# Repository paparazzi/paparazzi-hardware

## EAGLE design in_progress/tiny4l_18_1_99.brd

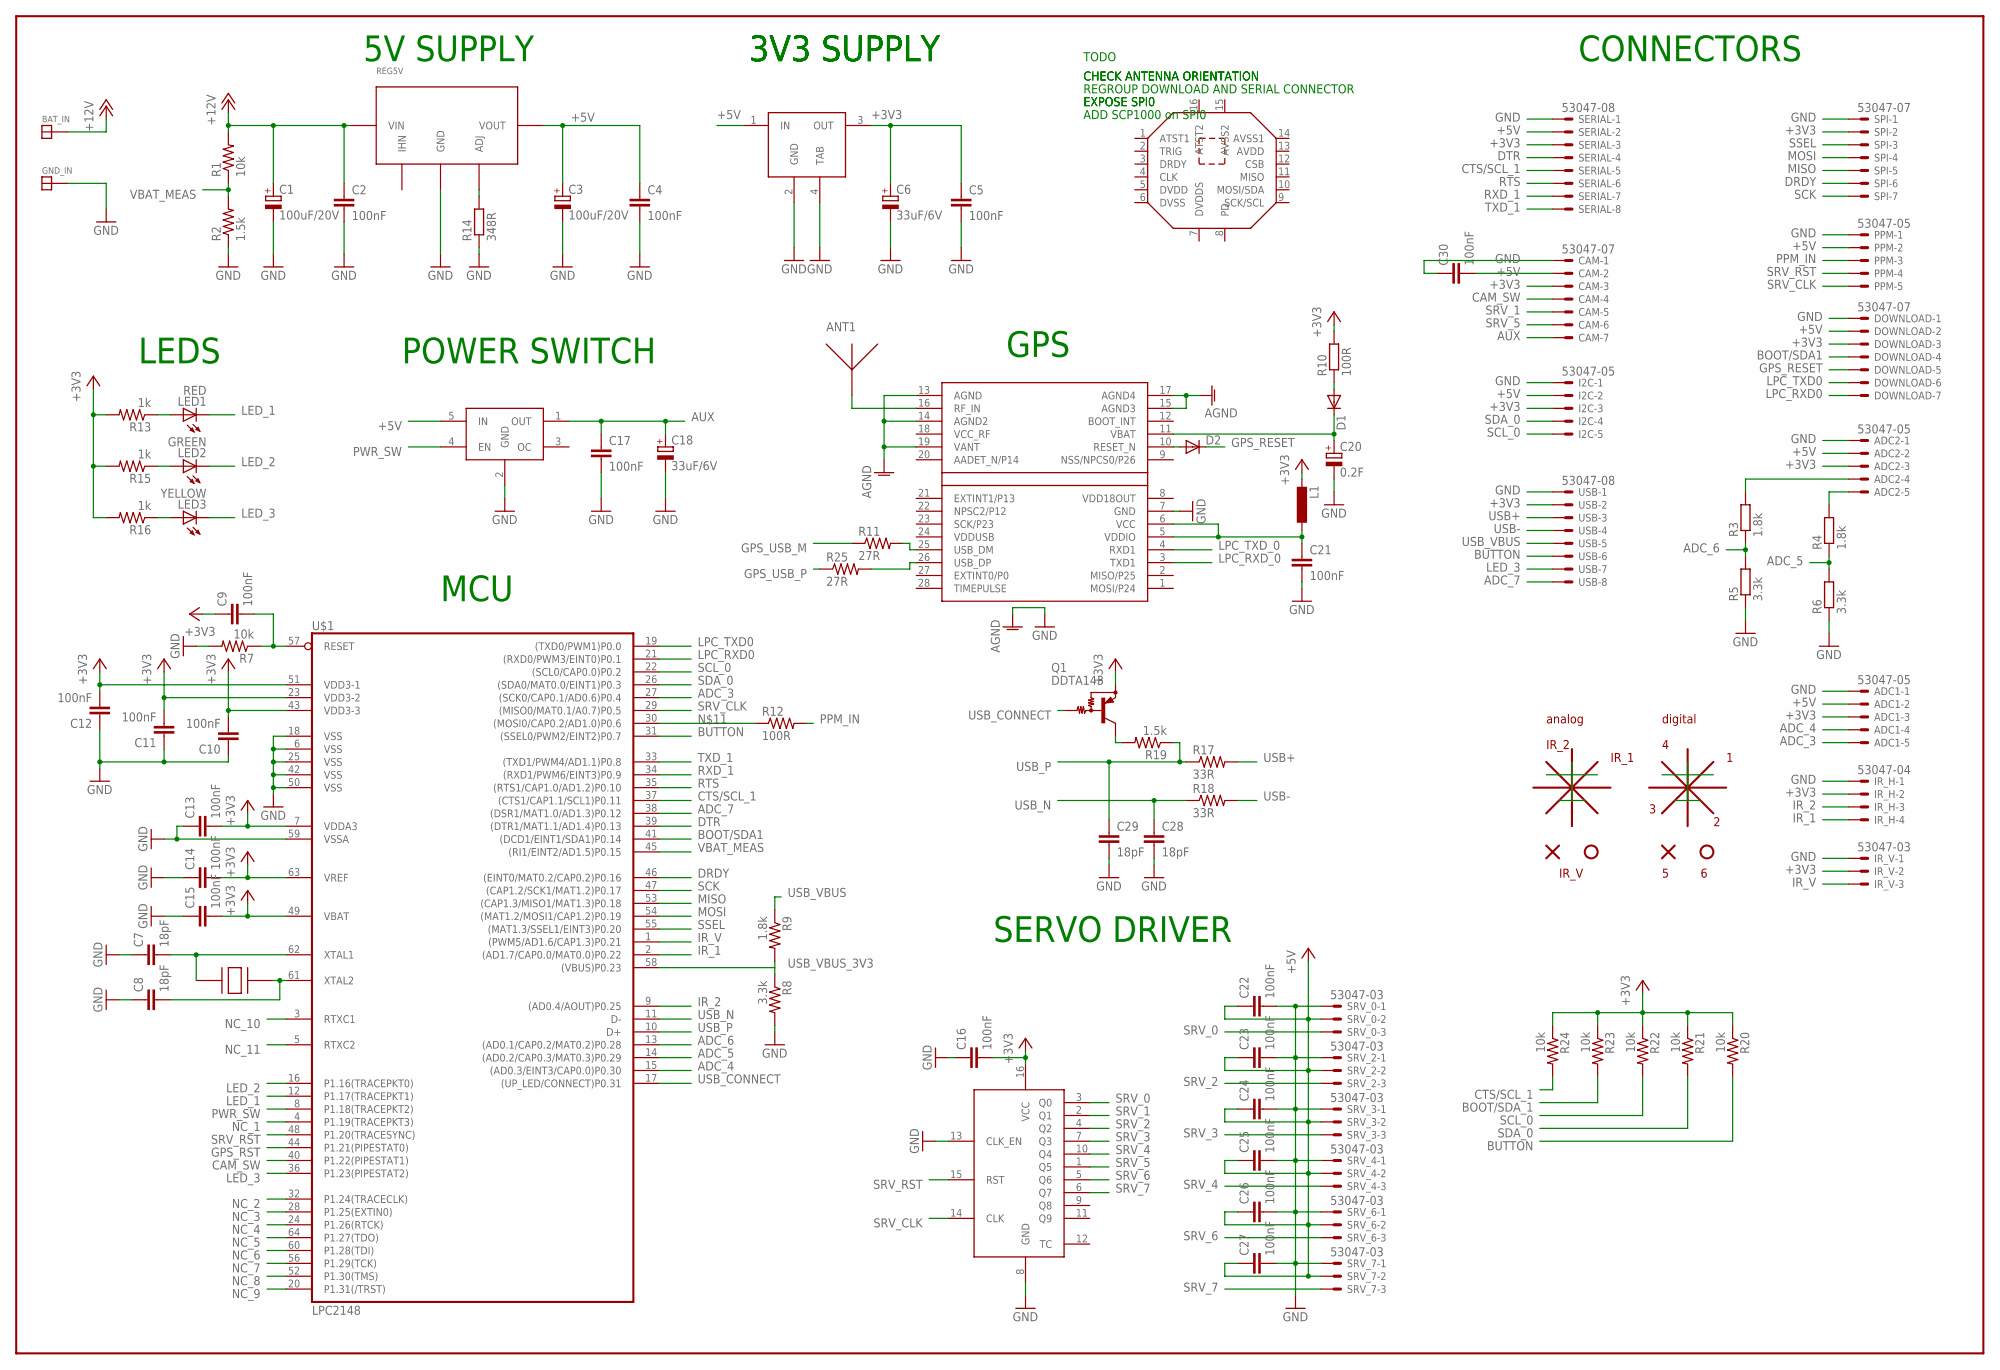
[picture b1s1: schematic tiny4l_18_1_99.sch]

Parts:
ADC1, ADC2: 53047-05
ANT1: GPS_ANT_1318; ANT_18
BAT_IN: SOLDER_PAD150_75; SOLD_PAD_150_75
C1, C3: 100uF/20V; SMC_D
C2, C4, C5, C9, C10, C11, C12, C13, C14, C15, C16, C17, C21, C22, C23, C24, C25, C26, C27, C30: 100nF; C0603
C6, C18: 33uF/6V; CT3216
C7, C8, C28, C29: 18pF; C0603
C20: 0.2F; PANA_J1_BIS
CAM: 53047-07
D1, D2: DIODE-SOD523; SOD523
DOWNLOAD: 53047-07
GND_IN: SOLDER_PAD150_75; SOLD_PAD_150_75
I2C: 53047-05
IR_H: 53047-04
IR_V: 53047-03
L1: L-EUL2012C; L2012C
LED1: RED; CHIP-LED0805
LED2: GREEN; CHIP-LED0805
LED3: YELLOW; CHIP-LED0805
PPM: 53047-05
Q1: DDTA143; SC59-BEC
R1, R7, R20, R21, R22, R23, R24: 10k; R0603
R2, R19: 1.5k; R0603
R3, R4, R9: 1.8k; R0603
R5, R6, R8: 3.3k; R0603
R10, R12: 100R; R0603
R11, R25: 27R; R0603
R13, R15, R16: 1k; R0603
R14: 348R; R0603
R17, R18: 33R; R0603
REG5V: PTH
SERIAL: 53047-08
SPI: 53047-07
SRV_0, SRV_2, SRV_3, SRV_4, SRV_6, SRV_7: 53047-03
U$1: LPC2148; SQFP-S-10X10-64
U$2: LEA-4P; LEA-LA
U$3: LM3940IMP-3.3; SOT223-R
U$4: CRYSTAL_CTS; CTS_CRYSTAL
U$5: CD4017B; TSSOP16
U$6: TPS2051B; SOT23-5L
U$7: SCP1000
USB: 53047-08

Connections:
+3V3: ADC1.3, ADC2.3, C5.1, C6.+, C9.1, C10.2, C11.2, C12.2, C13.2, C14.2, C15.2, C16.2, CAM.3, DOWNLOAD.3, I2C.3, IR_H.2, IR_V.2, L1.2, Q1.E, R10.2, R13.2, R15.2, R16.2, R20.1, R21.1, R22.1, R23.1, R24.1, SERIAL.3, SPI.2, U$1.7 (VDDA3), U$1.23 (VDD3-2), U$1.43 (VDD3-3), U$1.49 (VBAT), U$1.51 (VDD3-1), U$1.63 (VREF), U$3.3 (OUT), U$5.16 (VCC), USB.2
+5V: ADC1.2, ADC2.2, C3.+, C4.1, C22.1, C23.1, C24.1, C25.1, C26.1, C27.1, C30.2, CAM.2, DOWNLOAD.2, I2C.2, PPM.2, REG5V.P$3 (VOUT), SERIAL.2, SRV_0.2, SRV_2.2, SRV_3.2, SRV_4.2, SRV_6.2, SRV_7.2, U$3.1 (IN), U$6.5 (IN)
+12V: BAT_IN.P$1, C1.+, C2.1, R1.2, REG5V.P$1 (VIN)
ADC_3: ADC1.5, U$1.27 ((SCK0/CAP0.1/AD0.6)P0.4)
ADC_4: ADC1.4, U$1.15 ((AD0.3/EINT3/CAP0.0)P0.30)
ADC_5: R4.1, R6.2, U$1.14 ((AD0.2/CAP0.3/MAT0.3)P0.29)
ADC_6: R3.1, R5.2, U$1.13 ((AD0.1/CAP0.2/MAT0.2)P0.28)
ADC_7: U$1.38 ((DSR1/MAT1.0/AD1.3)P0.12), USB.8
AGND: U$2.13 (AGND), U$2.14 (AGND2), U$2.15 (AGND3), U$2.17 (AGND4), U$2.19 (VANT)
AUX: C17.1, C18.+, CAM.7, U$6.1 (OUT)
BOOT/SDA1: DOWNLOAD.4, U$1.41 ((DCD1/EINT1/SDA1)P0.14)
BOOT/SDA_1: R23.2
BUTTON: R20.2, U$1.31 ((SSEL0/PWM2/EINT2)P0.7), USB.6
CAM_SW: CAM.4, U$1.40 (P1.22(PIPESTAT1))
CTS/SCL_1: R24.2, SERIAL.5, U$1.37 ((CTS1/CAP1.1/SCL1)P0.11)
DRDY: SPI.6, U$1.46 ((EINT0/MAT0.2/CAP0.2)P0.16)
DTR: SERIAL.4, U$1.39 ((DTR1/MAT1.1/AD1.4)P0.13)
GND: ADC1.1, ADC2.1, C1.-, C2.2, C3.-, C4.2, C5.2, C6.-, C7.1, C8.1, C10.1, C11.1, C12.1, C13.1, C14.1, C15.1, C16.1, C17.2, C18.-, C20.MINUS (-), C21.2, C22.2, C23.2, C24.2, C25.2, C26.2, C27.2, C28.2, C29.2, C30.1, CAM.1, DOWNLOAD.1, GND_IN.P$1, I2C.1, IR_H.1, IR_V.1, PPM.1, R2.1, R5.1, R6.1, R7.2, R8.2, R14.1, REG5V.P$2 (GND), SERIAL.1, SPI.1, SRV_0.1, SRV_2.1, SRV_3.1, SRV_4.1, SRV_6.1, SRV_7.1, U$1.6 (VSS), U$1.18 (VSS), U$1.25 (VSS), U$1.42 (VSS), U$1.50 (VSS), U$1.59 (VSSA), U$2.7 (GND), U$3.2 (GND), U$3.4 (TAB), U$5.8 (GND), U$5.13 (CLK_EN), U$6.2 (GND), USB.1
GPS_RESET: D2.C, DOWNLOAD.5
GPS_RST: U$1.44 (P1.21(PIPESTAT0))
GPS_USB_M: R11.1
GPS_USB_P: R25.1
IR_1: IR_H.4, U$1.2 ((AD1.7/CAP0.0/MAT0.0)P0.22)
IR_2: IR_H.3, U$1.9 ((AD0.4/AOUT)P0.25)
IR_V: IR_V.3, U$1.1 ((PWM5/AD1.6/CAP1.3)P0.21)
LED_1: LED1.C, U$1.12 (P1.17(TRACEPKT1))
LED_2: LED2.C, U$1.16 (P1.16(TRACEPKT0))
LED_3: LED3.C, U$1.36 (P1.23(PIPESTAT2)), USB.7
LPC_RESET: C9.2, R7.1, U$1.57 (RESET)
LPC_RXD0: DOWNLOAD.7, U$1.21 ((RXD0/PWM3/EINT0)P0.1)
LPC_RXD_0: U$2.3 (TXD1)
LPC_TXD0: DOWNLOAD.6, U$1.19 ((TXD0/PWM1)P0.0)
LPC_TXD_0: U$2.4 (RXD1)
MISO: SPI.5, U$1.53 ((CAP1.3/MISO1/MAT1.3)P0.18)
MOSI: SPI.4, U$1.54 ((MAT1.2/MOSI1/CAP1.2)P0.19)
unnamed: LED1.A, R13.1
unnamed: C7.2, U$1.62 (XTAL1), U$4.P$1
unnamed: D1.A, R10.1
unnamed: C8.2, U$1.61 (XTAL2), U$4.P$3
unnamed: R14.2, REG5V.P$4 (ADJ)
unnamed: LED2.A, R15.1
unnamed: LED3.A, R16.1
unnamed: ANT1.P$1, U$2.16 (RF_IN)
unnamed: D2.A, U$2.10 (RESET_N)
unnamed: C20.PLUS (+), D1.C, U$2.11 (VBAT)
unnamed: R12.1, U$1.30 ((MOSI0/CAP0.2/AD1.0)P0.6)
unnamed: R8.1, R9.2
unnamed: C21.1, L1.1, U$2.5 (VDDIO), U$2.6 (VCC)
unnamed: Q1.C, R19.2
unnamed: R11.2, U$2.25 (USB_DM)
unnamed: R25.2, U$2.26 (USB_DP)
unnamed: ADC2.4, R3.2
unnamed: ADC2.5, R4.2
NC_1: U$1.4 (P1.19(TRACEPKT3))
NC_2: U$1.32 (P1.24(TRACECLK))
NC_3: U$1.28 (P1.25(EXTIN0))
NC_4: U$1.24 (P1.26(RTCK))
NC_5: U$1.64 (P1.27(TDO))
NC_6: U$1.60 (P1.28(TDI))
NC_7: U$1.56 (P1.29(TCK))
NC_8: U$1.52 (P1.30(TMS))
NC_9: U$1.20 (P1.31(/TRST))
NC_10: U$1.3 (RTXC1)
NC_11: U$1.5 (RTXC2)
PPM_IN: PPM.3, R12.2
PWR_SW: U$1.8 (P1.18(TRACEPKT2)), U$6.4 (EN)
RTS: SERIAL.6, U$1.35 ((RTS1/CAP1.0/AD1.2)P0.10)
RXD_1: SERIAL.7, U$1.34 ((RXD1/PWM6/EINT3)P0.9)
SCK: SPI.7, U$1.47 ((CAP1.2/SCK1/MAT1.2)P0.17)
SCL_0: I2C.5, R22.2, U$1.22 ((SCL0/CAP0.0)P0.2)
SDA_0: I2C.4, R21.2, U$1.26 ((SDA0/MAT0.0/EINT1)P0.3)
SRV_0: SRV_0.3, U$5.3 (Q0)
SRV_1: CAM.5, U$5.2 (Q1)
SRV_2: SRV_2.3, U$5.4 (Q2)
SRV_3: SRV_3.3, U$5.7 (Q3)
SRV_4: SRV_4.3, U$5.10 (Q4)
SRV_5: CAM.6, U$5.1 (Q5)
SRV_6: SRV_6.3, U$5.5 (Q6)
SRV_7: SRV_7.3, U$5.6 (Q7)
SRV_CLK: PPM.5, U$1.29 ((MISO0/MAT0.1/A0.7)P0.5), U$5.14 (CLK)
SRV_RST: PPM.4, U$1.48 (P1.20(TRACESYNC)), U$5.15 (RST)
SSEL: SPI.3, U$1.55 ((MAT1.3/SSEL1/EINT3)P0.20)
TXD_1: SERIAL.8, U$1.33 ((TXD1/PWM4/AD1.1)P0.8)
USB+: R17.2, USB.3
USB-: R18.2, USB.4
USB_CONNECT: Q1.B, U$1.17 ((UP_LED/CONNECT)P0.31)
USB_N: C28.1, R18.1, U$1.11 (D-)
USB_P: C29.1, R17.1, R19.1, U$1.10 (D+)
USB_VBUS: R9.1, USB.5
USB_VBUS_3V3: U$1.58 ((VBUS)P0.23)
VBAT_MEAS: R1.1, R2.2, U$1.45 ((RI1/EINT2/AD1.5)P0.15)
VCC_RF: U$2.18 (VCC_RF)
VDD18OUT: U$2.8 (VDD18OUT)

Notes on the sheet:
5V SUPPLY
3V3 SUPPLY
MCU
GPS
LEDS
POWER SWITCH
SERVO DRIVER
CONNECTORS
CHECK ANTENNA ORIENTATION
TODO
REGROUP DOWNLOAD AND SERIAL CONNECTOR
EXPOSE SPI0
ADD SCP1000 on SPI0
IR_V
IR_2
IR_1
analog
digital

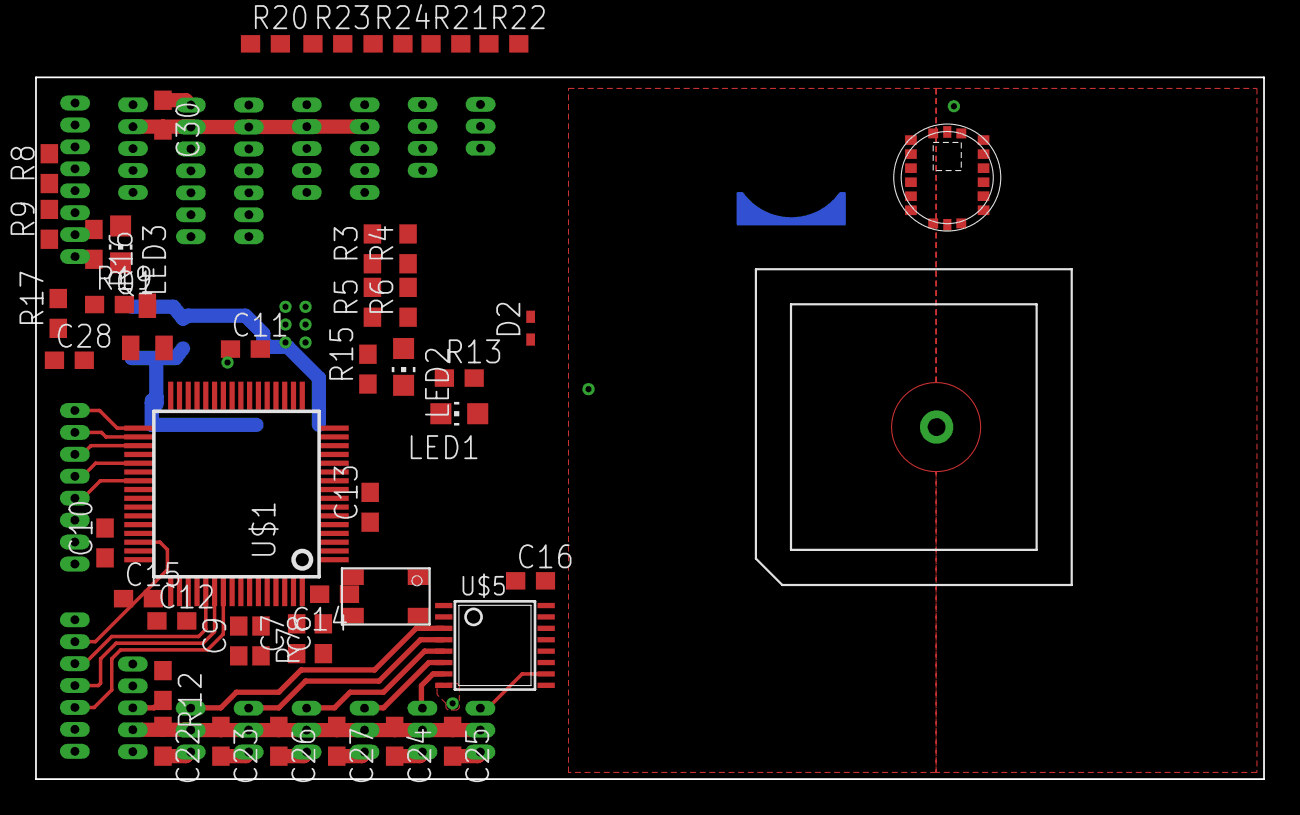
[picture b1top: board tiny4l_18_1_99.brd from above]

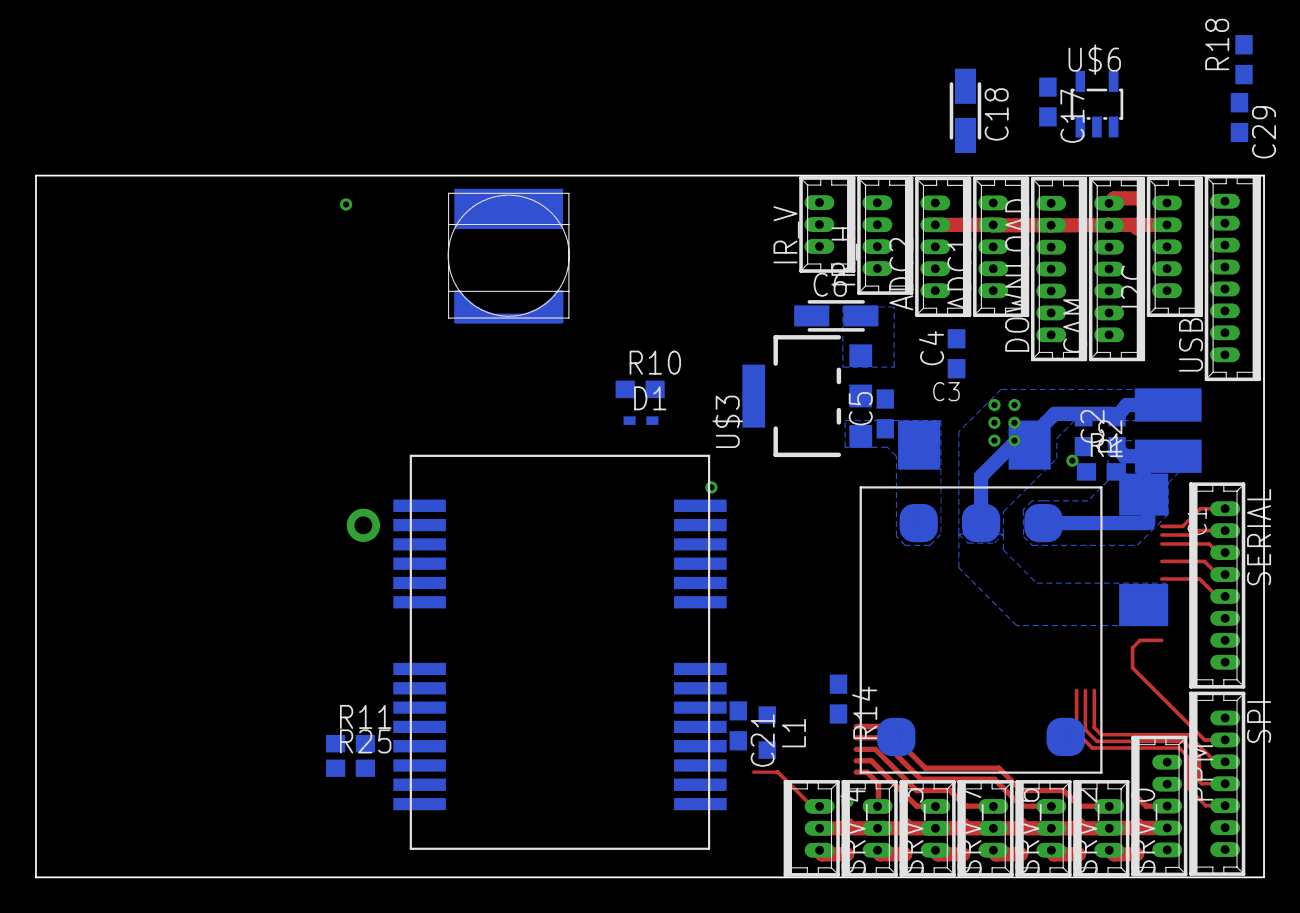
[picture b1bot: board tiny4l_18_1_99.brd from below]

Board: 4 copper layers, 70.0 x 40.0 mm, 89 parts (43 on the bottom side), 73 nets.

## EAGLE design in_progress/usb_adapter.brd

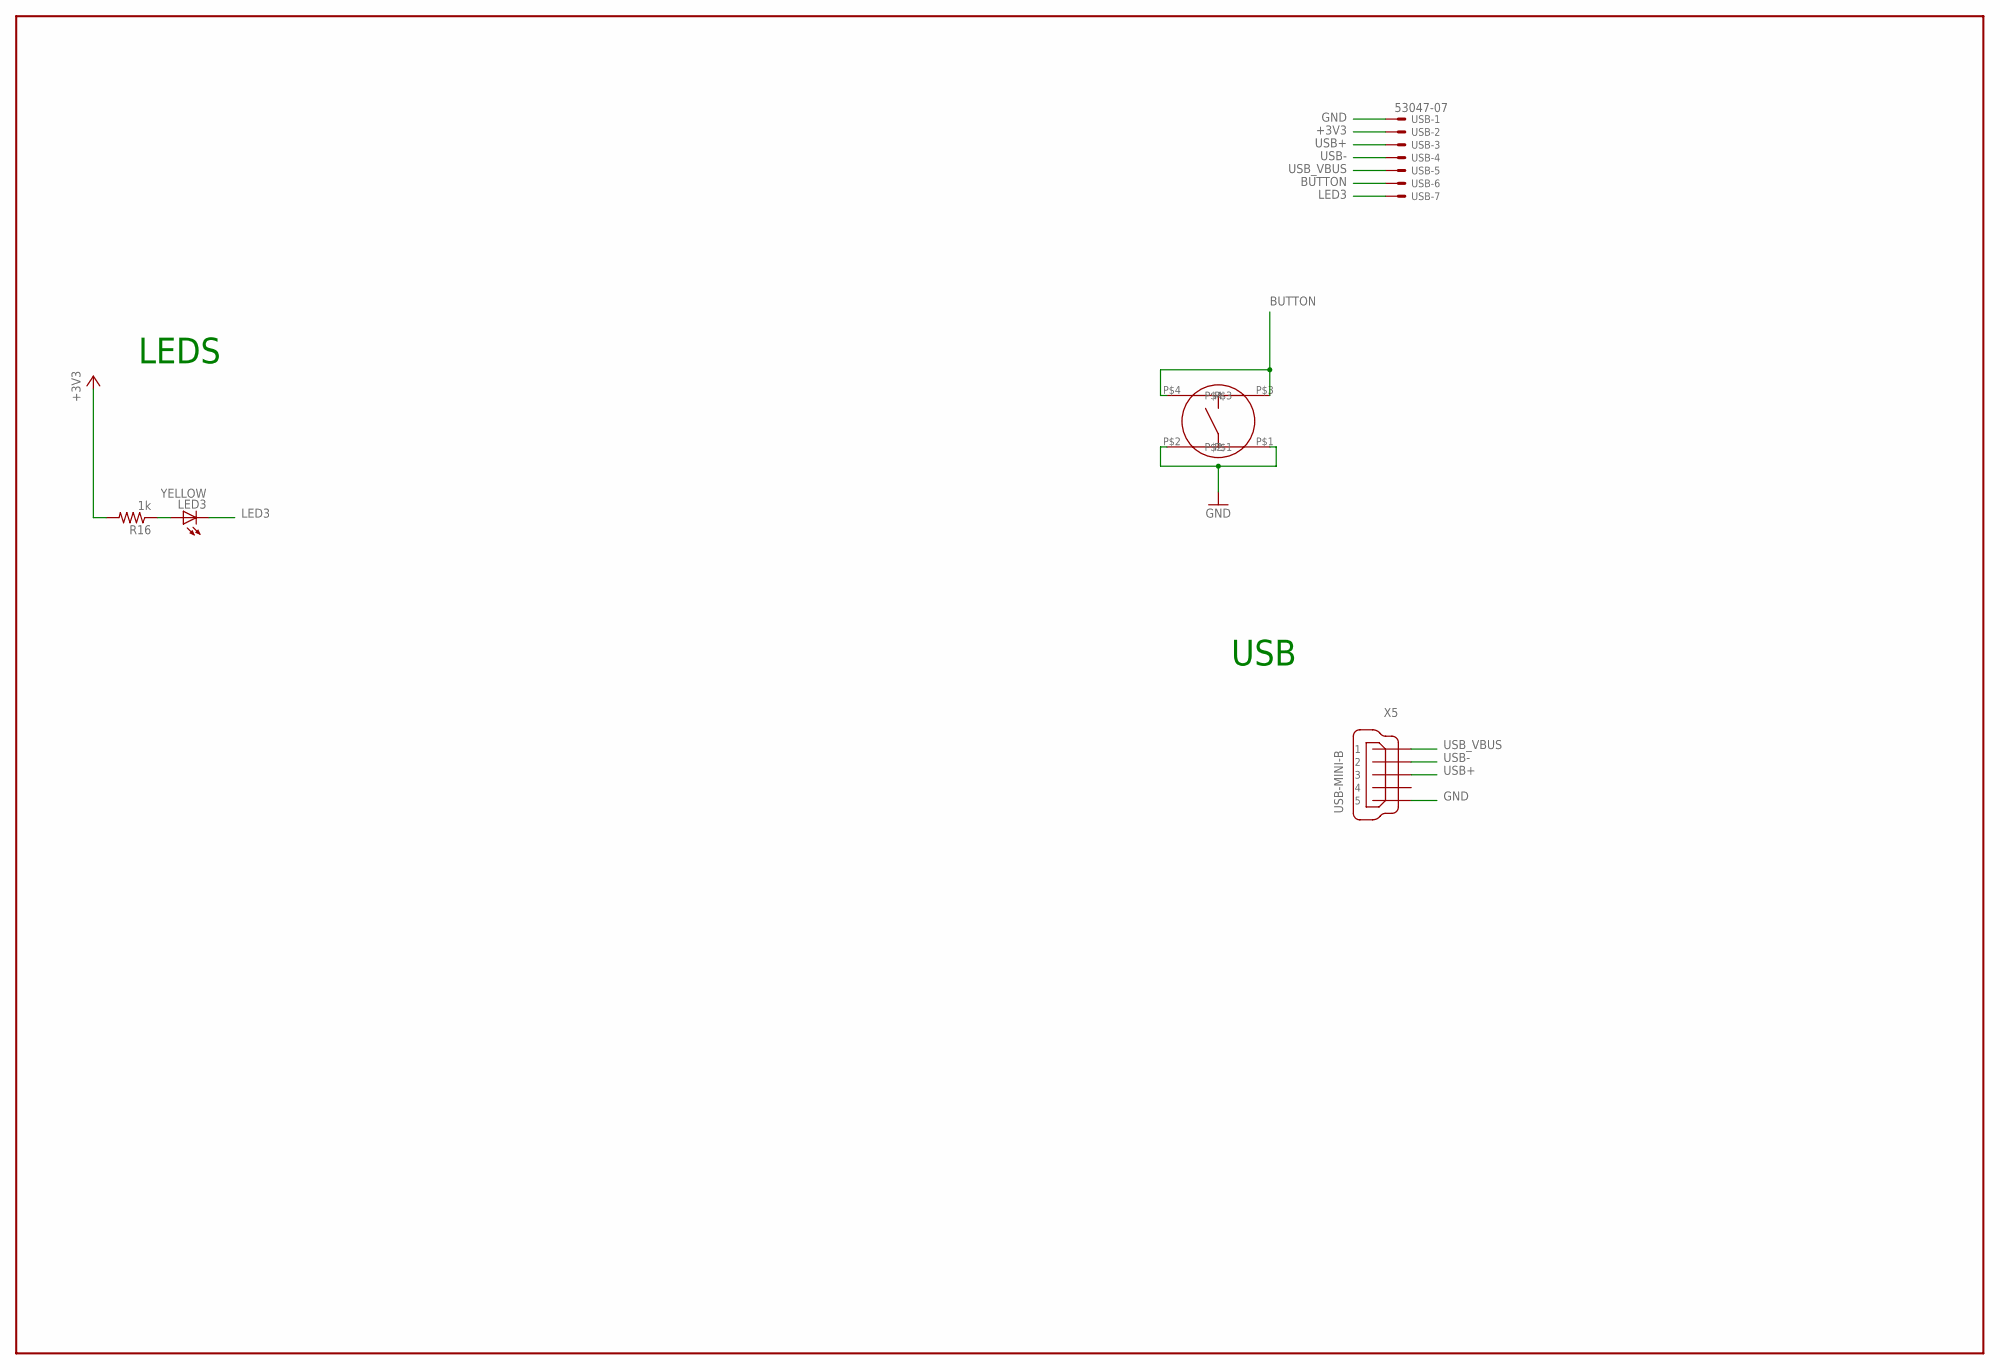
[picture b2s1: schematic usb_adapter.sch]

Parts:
LED3: YELLOW; CHIP-LED0805
R16: 1k; R0603@1
SW1: B3S
USB: 53047-07
X5: USB-MINI-B; UX60-MB-5ST

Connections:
+3V3: R16.2, USB.2
BUTTON: SW1.P$3, SW1.P$4, USB.6
GND: SW1.P$1, SW1.P$2, USB.1, X5.5
LED3: LED3.C, USB.7
unnamed: LED3.A, R16.1
USB+: USB.3, X5.3
USB-: USB.4, X5.2
USB_VBUS: USB.5, X5.1

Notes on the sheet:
LEDS
USB

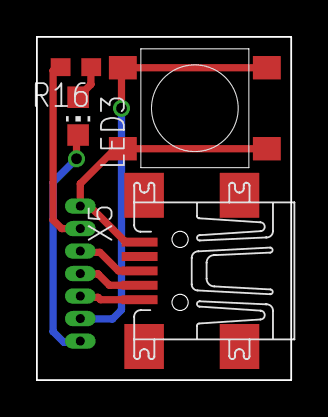
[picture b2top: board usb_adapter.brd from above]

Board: 4 copper layers, 14.1 x 19.1 mm, 5 parts (1 on the bottom side), 8 nets.

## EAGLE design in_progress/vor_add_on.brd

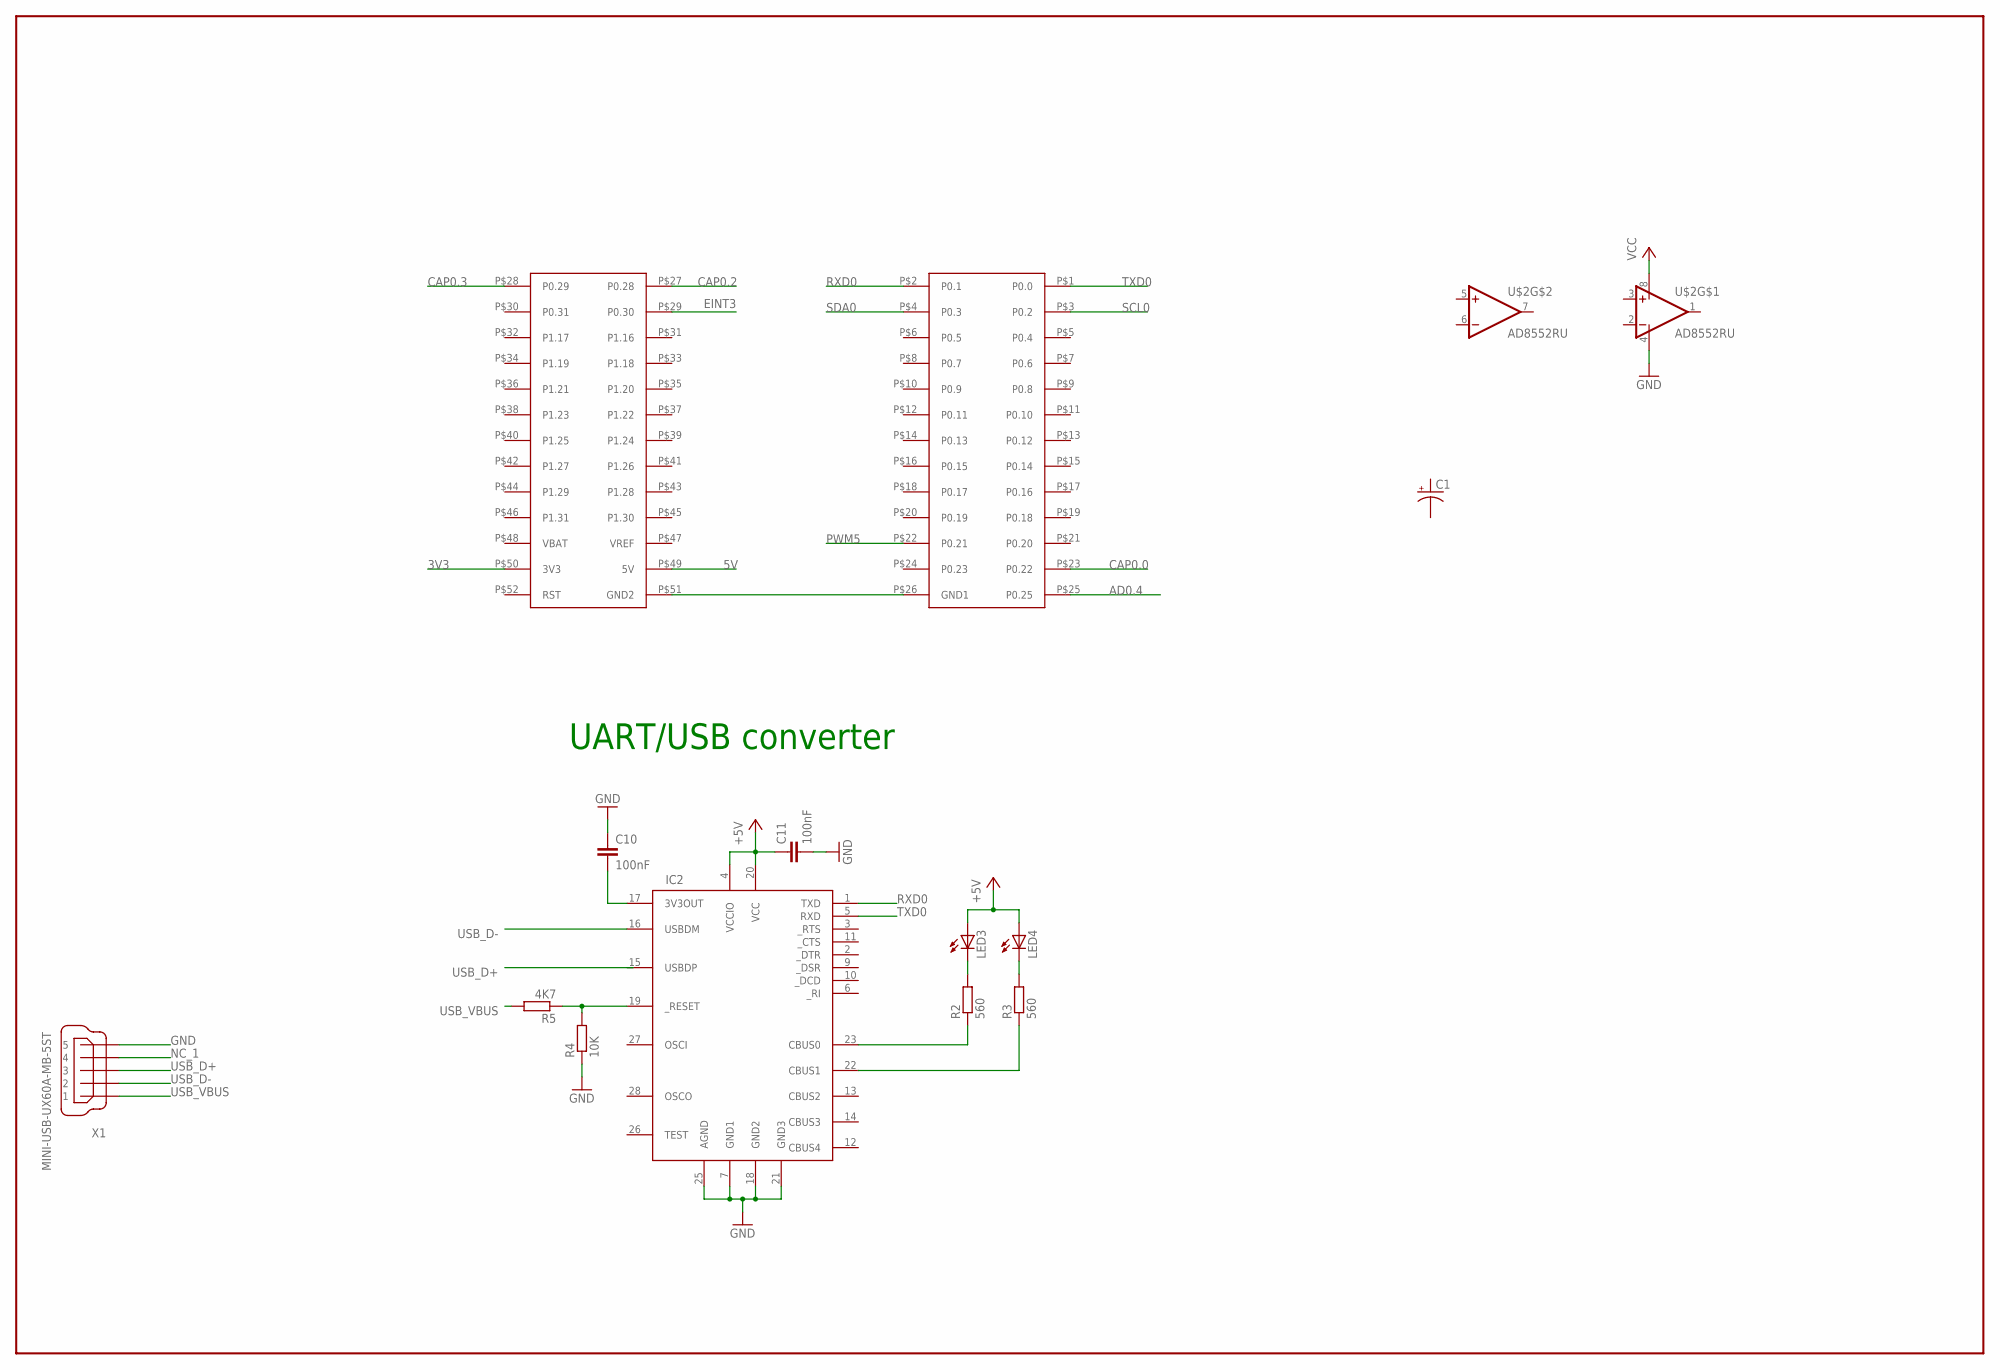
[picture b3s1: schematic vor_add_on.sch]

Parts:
C1: CPOL-USCT7343; CT7343
C10, C11: 100nF; C0603K
IC2: FT232RL; SSOP28DB
LED3, LED4: LEDCHIPLED_0805; CHIPLED_0805
R2, R3: 560; R0805
R4: 10K; R0603
R5: 4K7; R0603
U$1: OLIMEX_2148
U$2: AD8552RU; TSSOP8
X1: MINI-USB-UX60A-MB-5ST; UX60A-MB-5ST

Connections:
3V3: U$1.P$50 (3V3)
5V: U$1.P$49 (5V)
+5V: C11.1, IC2.4 (VCCIO), IC2.20 (VCC), LED3.A, LED4.A
AD0.4: U$1.P$25 (P0.25)
CAP0.0: U$1.P$23 (P0.22)
CAP0.2: U$1.P$27 (P0.28)
CAP0.3: U$1.P$28 (P0.29)
EINT3: U$1.P$29 (P0.30)
GND: C10.1, C11.2, IC2.7 (GND1), IC2.18 (GND2), IC2.21 (GND3), IC2.25 (AGND), R4.1, U$1.P$26 (GND1), U$1.P$51 (GND2), U$2.4 (V-), X1.5
unnamed: IC2.23 (CBUS0), R2.1
unnamed: IC2.22 (CBUS1), R3.1
unnamed: LED3.C, R2.2
unnamed: LED4.C, R3.2
unnamed: IC2.19 (_RESET), R4.2, R5.1
unnamed: C10.2, IC2.17 (3V3OUT)
NC_1: X1.4
PWM5: U$1.P$22 (P0.21)
RXD0: IC2.1 (TXD), U$1.P$2 (P0.1)
SCL0: U$1.P$3 (P0.2)
SDA0: U$1.P$4 (P0.3)
TXD0: IC2.5 (RXD), U$1.P$1 (P0.0)
USB_D+: X1.3
USB_D-: IC2.16 (USBDM), X1.2
USB_VBUS: R5.2, X1.1
VCC: U$2.8 (V+)

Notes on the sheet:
UART/USB converter

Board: 2 copper layers, 13 parts (2 on the bottom side), 12 nets, no tracks yet.

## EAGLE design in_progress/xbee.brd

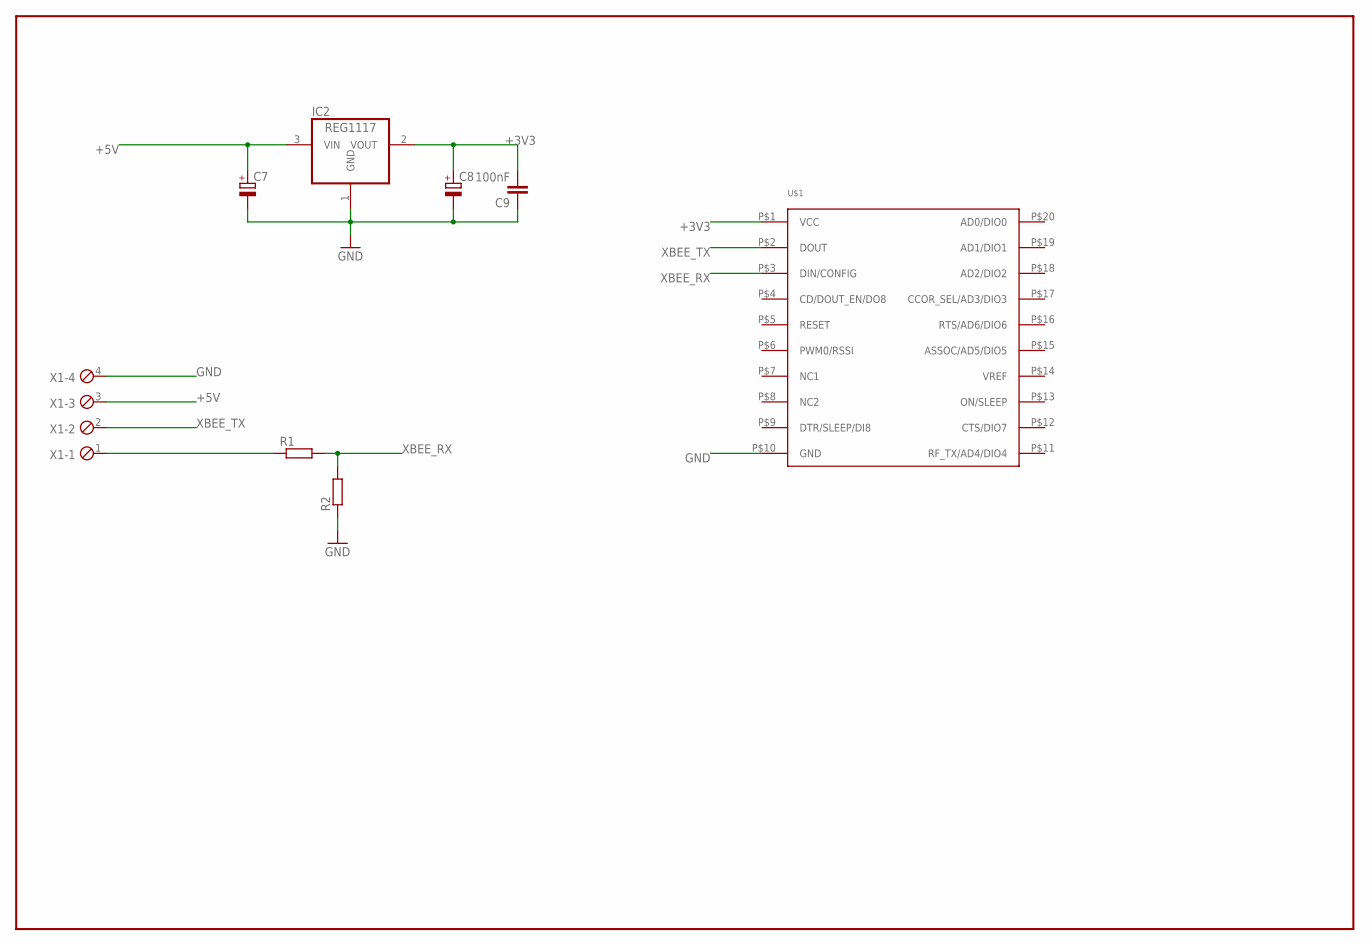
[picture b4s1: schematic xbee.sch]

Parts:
C7: CPOL-EUA/3216-18R; A/3216-18R
C8: CPOL-EUB/3528-21R; B/3528-21R
C9: 100nF; C0603
IC2: REG1117; SOT223
R1, R2: R-EU_R1206W; R1206W
U$1: XBEEPRO; XBEE
X1: MPT4; 4POL254

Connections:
+3V3: C8.+, C9.2, IC2.2 (VOUT), U$1.P$1 (VCC)
+5V: C7.+, IC2.3 (VIN), X1.3
GND: C7.-, C8.-, C9.1, IC2.1 (GND), R2.1, U$1.P$10 (GND), X1.4
unnamed: R1.1, X1.1
XBEE_RX: R1.2, R2.2, U$1.P$3 (DIN/CONFIG)
XBEE_TX: U$1.P$2 (DOUT), X1.2

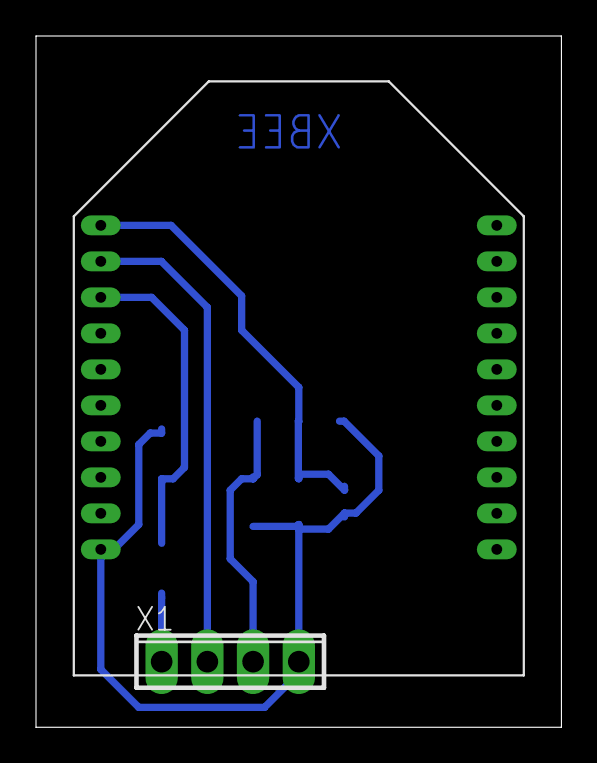
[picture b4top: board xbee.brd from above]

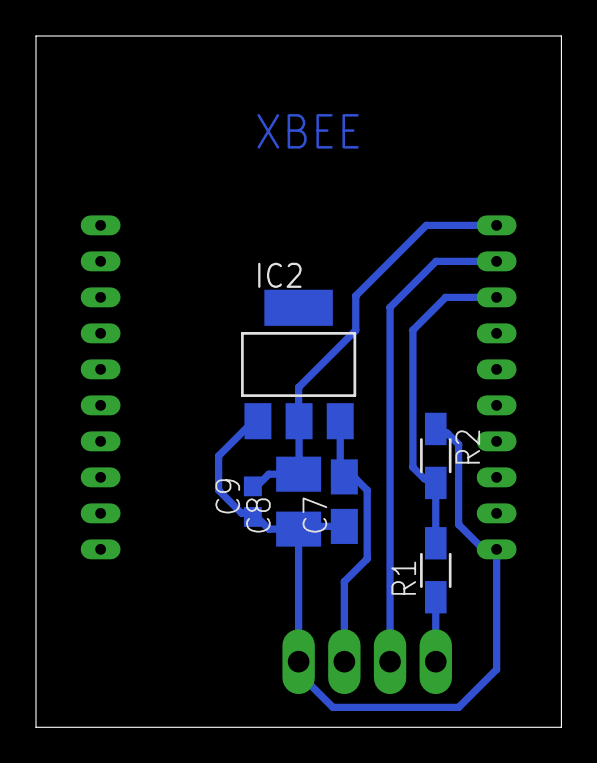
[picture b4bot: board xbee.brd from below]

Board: 2 copper layers, 29.2 x 38.4 mm, 8 parts (6 on the bottom side), 6 nets.

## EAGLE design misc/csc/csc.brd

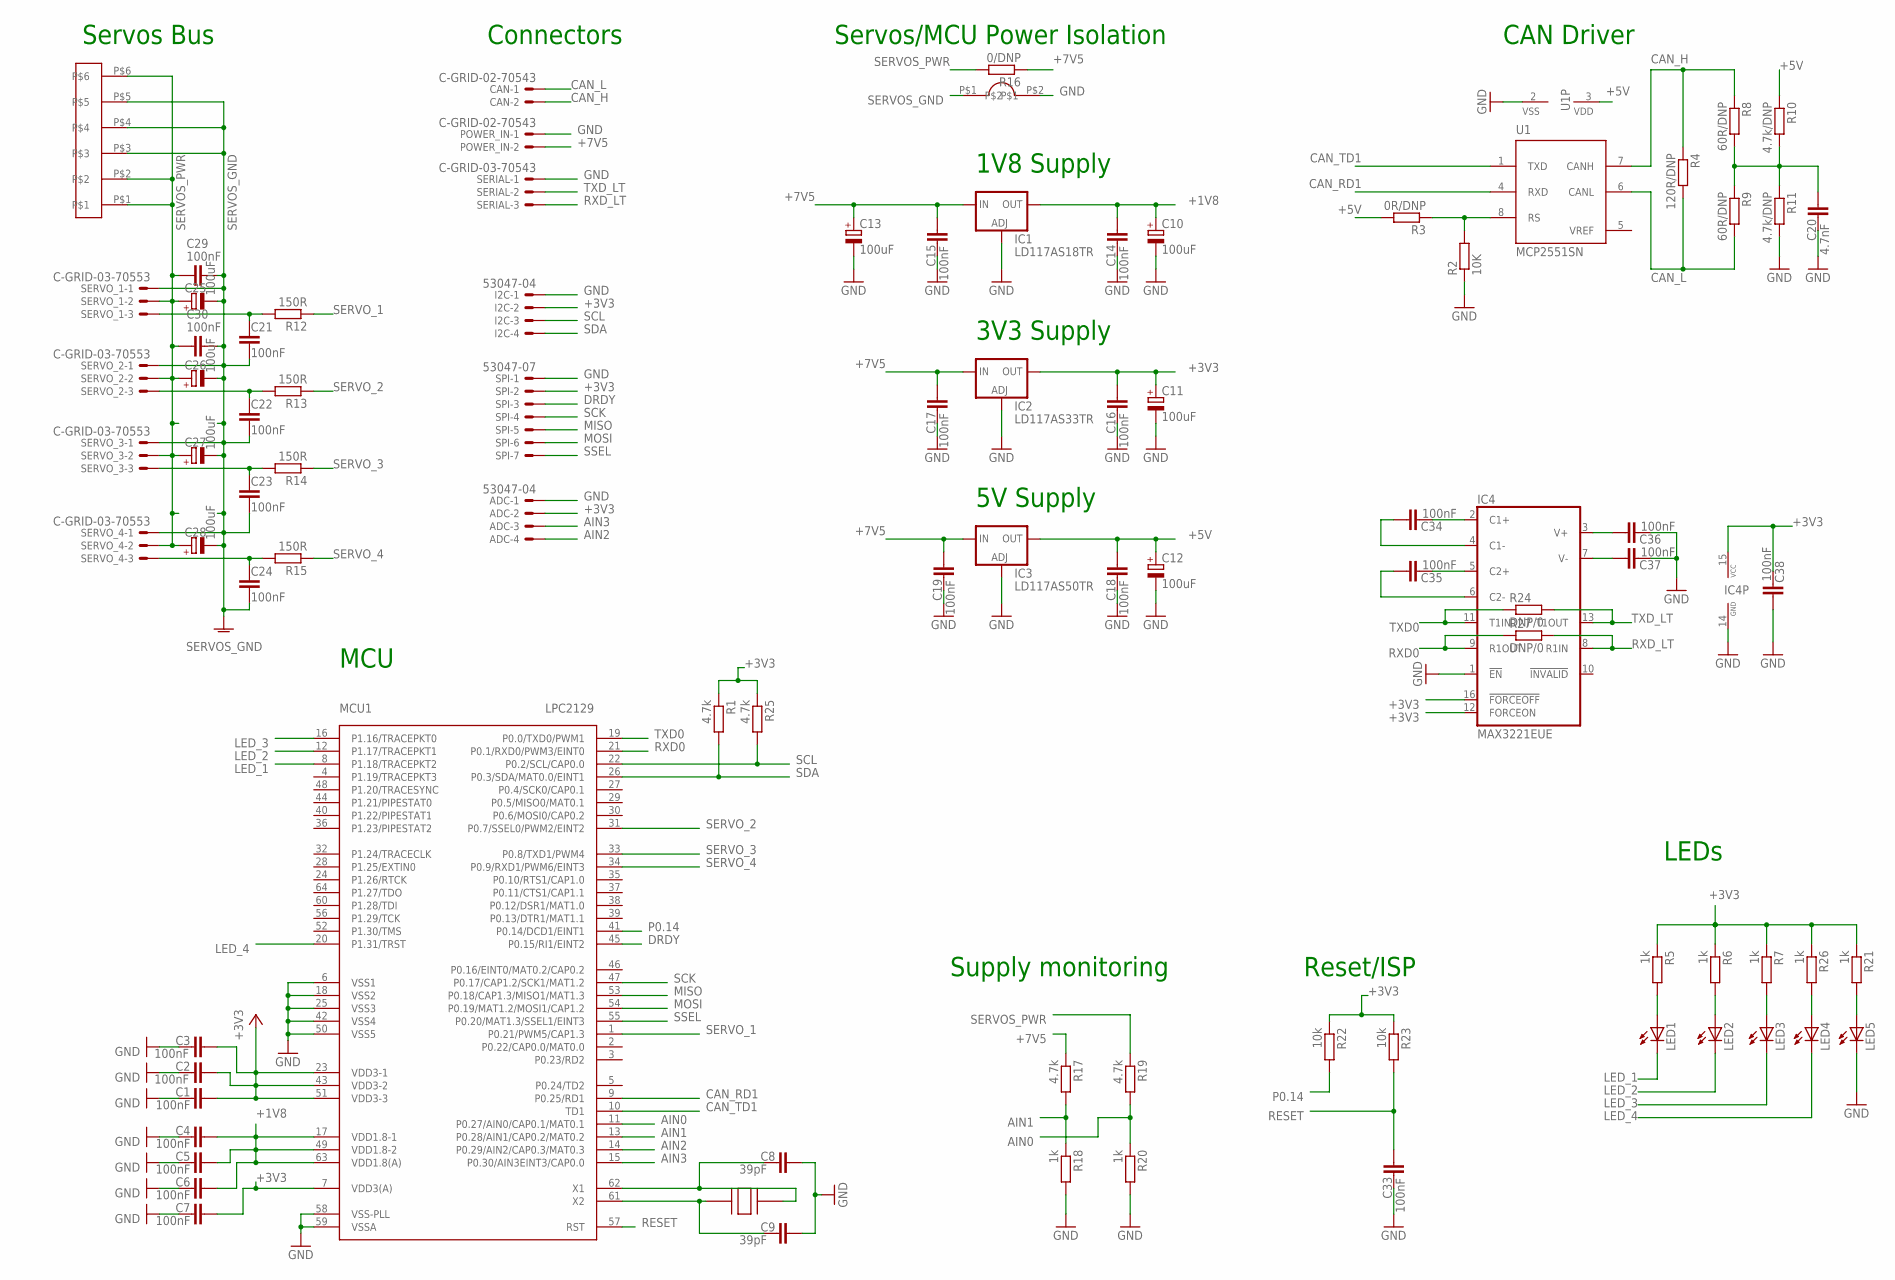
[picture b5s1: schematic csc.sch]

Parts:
ADC: 53047-04
C1, C2, C3, C4, C5, C6, C7, C14, C15, C16, C17, C18, C19, C21, C22, C23, C24, C29, C30, C33, C34, C35, C36, C37, C38: 100nF; C0603K
C8, C9: 39pF; C0603K
C10, C11, C12: 100uF; CT6032
C13: 100uF; CT7343
C20: 4.7nF; C0603K
C25, C26, C27, C28: 100uF; E/7260-38W
CAN: C-GRID-02-70543; 70543-02
I2C: 53047-04
IC1: LD117AS18TR; SOT223
IC2: LD117AS33TR; SOT223
IC3: LD117AS50TR; SOT223
IC4: MAX3221EUE; TSSOP16
LED1, LED2, LED3, LED4, LED5: LEDCHIP-LED0805; CHIP-LED0805
MCU1: LPC2129; SQFP-S-10X10-64
POWER_IN: C-GRID-02-70543; 70543-02
R1, R17, R19, R25: 4.7k; R0603
R2: 10K; R0603
R3: 0R/DNP; R0603
R4: 120R/DNP; R0603
R5, R6, R7, R18, R20, R21, R26: 1k; R0603
R8, R9: 60R/DNP; R0603
R10, R11: 4.7k/DNP; R0603
R12, R13, R14, R15: 150R; R0603
R16: 0/DNP; R0603
R22, R23: 10k; R0603
R24, R27: DNP/0; R0603
SERIAL: C-GRID-03-70543; 70543-03
SERVO_1, SERVO_2, SERVO_3, SERVO_4: C-GRID-03-70553; 70553-03
SPI: 53047-07
U1: MCP2551SN; SO-08
U$1: CRYSTAL_CTS; CTS_CRYSTAL
U$2: CON_MPX
U$3: NULL_DEV

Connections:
+1V8: C4.2, C5.2, C6.2, C10.+, C14.2, IC1.4 (OUT), MCU1.17 (VDD1.8-1), MCU1.49 (VDD1.8-2), MCU1.63 (VDD1.8(A))
+3V3: ADC.2, C1.2, C2.2, C3.2, C7.2, C11.+, C16.2, C38.1, I2C.2, IC2.4 (OUT), IC4.12 (FORCEON), IC4.15 (VCC), IC4.16 (!FORCEOFF), MCU1.7 (VDD3(A)), MCU1.23 (VDD3-1), MCU1.43 (VDD3-2), MCU1.51 (VDD3-3), R1.1, R5.1, R6.1, R7.1, R21.1, R22.1, R23.1, R25.1, R26.1, SPI.2
+5V: C12.+, C18.2, IC3.4 (OUT), R3.2, R10.1, U1.3 (VDD)
+7V5: C13.+, C15.2, C17.2, C19.2, IC1.3 (IN), IC2.3 (IN), IC3.3 (IN), POWER_IN.2, R16.1, R17.1
AIN0: MCU1.11 (P0.27/AIN0/CAP0.1/MAT0.1), R19.2, R20.1
AIN1: MCU1.13 (P0.28/AIN1/CAP0.2/MAT0.2), R17.2, R18.1
AIN2: ADC.4, MCU1.14 (P0.29/AIN2/CAP0.3/MAT0.3)
AIN3: ADC.3, MCU1.15 (P0.30/AIN3EINT3/CAP0.0)
CAN_H: CAN.2, R4.1, R8.1, U1.7 (CANH)
CAN_L: CAN.1, R4.2, R9.2, U1.6 (CANL)
CAN_RD1: MCU1.9 (P0.25/RD1), U1.4 (RXD)
CAN_TD1: MCU1.10 (TD1), U1.1 (TXD)
DRDY: MCU1.45 (P0.15/RI1/EINT2), SPI.3
GND: ADC.1, C1.1, C2.1, C3.1, C4.1, C5.1, C6.1, C7.1, C8.2, C9.2, C10.-, C11.-, C12.-, C13.-, C14.1, C15.1, C16.1, C17.1, C18.1, C19.1, C20.1, C33.1, C36.1, C37.1, C38.2, I2C.1, IC1.1 (ADJ), IC2.1 (ADJ), IC3.1 (ADJ), IC4.1 (!EN), IC4.14 (GND), LED5.C, MCU1.6 (VSS1), MCU1.18 (VSS2), MCU1.25 (VSS3), MCU1.42 (VSS4), MCU1.50 (VSS5), MCU1.58 (VSS-PLL), MCU1.59 (VSSA), POWER_IN.1, R2.1, R11.2, R18.2, R20.2, SERIAL.1, SPI.1, U1.2 (VSS), U$3.P$2
LED_1: LED1.C, MCU1.8 (P1.18/TRACEPKT2)
LED_2: LED2.C, MCU1.12 (P1.17/TRACEPKT1)
LED_3: LED3.C, MCU1.16 (P1.16/TRACEPKT0)
LED_4: LED4.C, MCU1.20 (P1.31/TRST)
MISO: MCU1.53 (P0.18/CAP1.3/MISO1/MAT1.3), SPI.5
MOSI: MCU1.54 (P0.19/MAT1.2/MOSI1/CAP1.2), SPI.6
unnamed: C8.1, MCU1.62 (X1), U$1.P$1
unnamed: C9.1, MCU1.61 (X2), U$1.P$3
unnamed: R2.2, R3.1, U1.8 (RS)
unnamed: LED1.A, R5.2
unnamed: LED2.A, R6.2
unnamed: LED3.A, R7.2
unnamed: LED5.A, R21.2
unnamed: C20.2, R8.2, R9.1, R10.2, R11.1
unnamed: C21.2, R12.2, SERVO_1.3
unnamed: C22.2, R13.2, SERVO_2.3
unnamed: C23.2, R14.2, SERVO_3.3
unnamed: C24.2, R15.2, SERVO_4.3
unnamed: C34.1, IC4.2 (C1+)
unnamed: LED4.A, R26.2
unnamed: C34.2, IC4.4 (C1-)
unnamed: C35.1, IC4.5 (C2+)
unnamed: C35.2, IC4.6 (C2-)
unnamed: C36.2, IC4.3 (V+)
unnamed: C37.2, IC4.7 (V-)
P0.14: MCU1.41 (P0.14/DCD1/EINT1), R22.2
RESET: C33.2, MCU1.57 (RST), R23.2
RXD0: IC4.9 (R1OUT), MCU1.21 (P0.1/RXD0/PWM3/EINT0), R27.1
RXD_LT: IC4.8 (R1IN), R27.2, SERIAL.3
SCK: MCU1.47 (P0.17/CAP1.2/SCK1/MAT1.2), SPI.4
SCL: I2C.3, MCU1.22 (P0.2/SCL/CAP0.0), R25.2
SDA: I2C.4, MCU1.26 (P0.3/SDA/MAT0.0/EINT1), R1.2
SERVOS_GND: C21.1, C22.1, C23.1, C24.1, C25.-, C26.-, C27.-, C28.-, C29.1, C30.1, SERVO_1.1, SERVO_2.1, SERVO_3.1, SERVO_4.1, U$2.P$3, U$2.P$4, U$2.P$5, U$3.P$1
SERVOS_PWR: C25.+, C26.+, C27.+, C28.+, C29.2, C30.2, R16.2, R19.1, SERVO_1.2, SERVO_2.2, SERVO_3.2, SERVO_4.2, U$2.P$1, U$2.P$2, U$2.P$6
SERVO_1: MCU1.1 (P0.21/PWM5/CAP1.3), R12.1
SERVO_2: MCU1.31 (P0.7/SSEL0/PWM2/EINT2), R13.1
SERVO_3: MCU1.33 (P0.8/TXD1/PWM4), R14.1
SERVO_4: MCU1.34 (P0.9/RXD1/PWM6/EINT3), R15.1
SSEL: MCU1.55 (P0.20/MAT1.3/SSEL1/EINT3), SPI.7
TXD0: IC4.11 (T1IN), MCU1.19 (P0.0/TXD0/PWM1), R24.1
TXD_LT: IC4.13 (T1OUT), R24.2, SERIAL.2
VREF: U1.5 (VREF)

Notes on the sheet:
3V3 Supply
1V8 Supply
5V Supply
MCU
Servos Bus
CAN Driver
LEDs
Connectors
Servos/MCU Power Isolation
Supply monitoring
Reset/ISP
